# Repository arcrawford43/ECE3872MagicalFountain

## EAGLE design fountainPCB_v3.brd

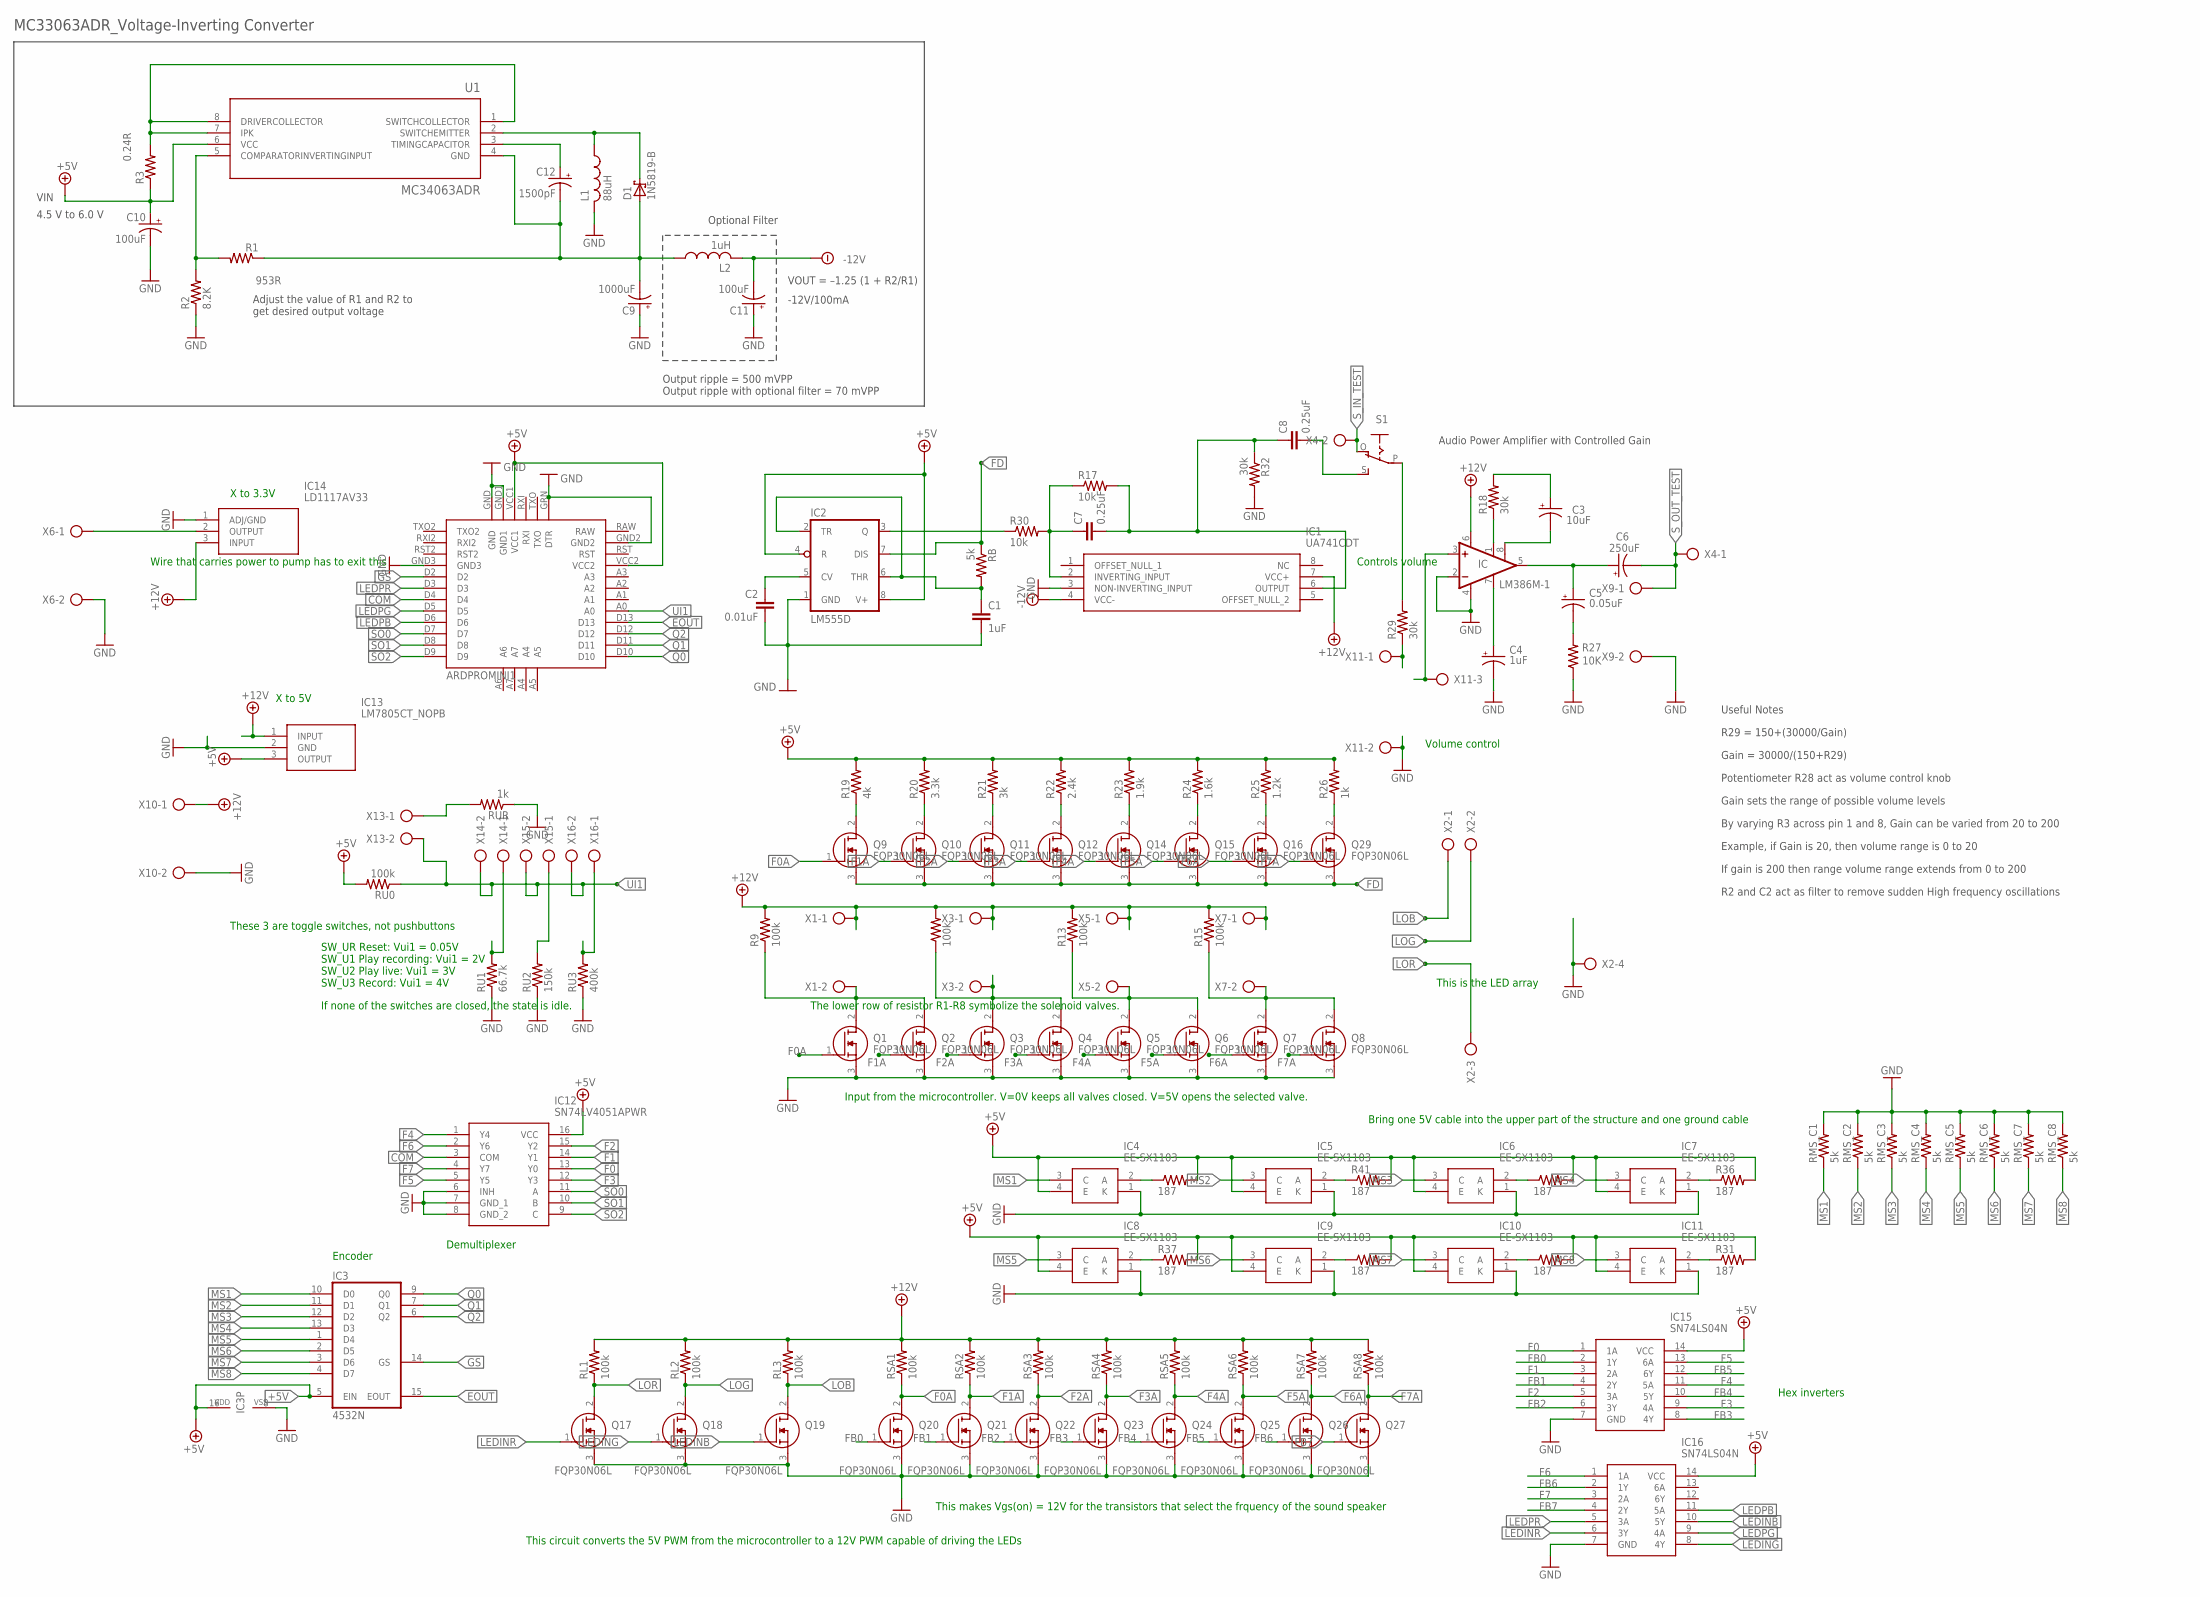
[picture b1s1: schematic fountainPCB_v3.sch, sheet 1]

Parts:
ARDPROMINI1: ARDUINOPROMINI
C1: 1uF; C0805
C2: 0.01uF; C0805
C3: 10uF; 085CS_1AR
C4: 1uF; 085CS_1AR
C5: 0.05uF; 085CS_1AR
C6: 250uF; 085CS_1AR
C7, C8: 0.25uF; C0805
C9: 1000uF; E7,5-16
C10, C11: 100uF; E2,5-6E
C12: 1500pF; E2,5-6E
D1: 1N5819-B; DO41-7.6
IC: LM386M-1; SO08
IC1: UA741CDT; SOIC127P600X175-8N
IC2: LM555D; SO08
IC3: 4532N; DIL16
IC4, IC5, IC6, IC7, IC8, IC9, IC10, IC11: EE-SX1103; EESX1103
IC12: SN74LV4051APWR; SOP65P640X120-16N
IC13: LM7805CT_NOPB; TO254P470X1028X1955-3P
IC14: LD1117AV33; TO255P460X1020X2008-3P
IC15, IC16: SN74LS04N; DIP794W53P254L1930H508Q14N
L1: 88uH; L3216C
L2: 1uH; L3216C
Q1, Q2, Q3, Q4, Q5, Q6, Q7, Q8, Q9, Q10, Q11, Q12, Q14, Q15, Q16, Q17, Q18, Q19, Q20, Q21, Q22, Q23, Q24, Q25, Q26, Q27, Q29: FQP30N06L; TO254P470X1016X2019-3P
R1: 953R; M0805
R2: 8.2K; M0805
R3: 0.24R; M0805
R9, R11, R13, R15: 100k; R0805
R17, R30: 10k; R0805
R18, R29, R32: 30k; R0805
R19: 4k; R0805
R20: 3.3k; R0805
R21: 3k; R0805
R22: 2.4k; R0805
R23: 1.9k; R0805
R24: 1.6k; R0805
R25: 1.2k; R0805
R26: 1k; R0805
R27: 10K; M0805
R31, R34, R36, R37, R40, R41, R42, R44: 187; R0805
RB: 5k; R0805
RL1, RL2, RL3: 100k; R0805
RMS_C1, RMS_C2, RMS_C3, RMS_C4, RMS_C5, RMS_C6, RMS_C7, RMS_C8: 5k; R0805
RSA1, RSA2, RSA3, RSA4, RSA5, RSA6, RSA7, RSA8: 100k; R0805
RU0: 100k; R0805
RU1: 66.7k; R0805
RU2: 150k; R0805
RU3: 400k; R0805
RUR: 1k; R0805
S1: EG1218S; EG1218
U1: MC34063ADR; D8
X1, X3, X4, X5, X6, X7, X9, X10, X13, X14, X15, X16: AK300/2
X2: AK300/4
X11: AK300/3

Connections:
+5V: ARDPROMINI1.VCC1, ARDPROMINI1.VCC2, C10.+, IC2.4 (R), IC2.8 (V+), IC3.5 (EIN), IC3.16 (VDD), IC4.4 (E), IC5.4 (E), IC6.4 (E), IC7.4 (E), IC8.4 (E), IC9.4 (E), IC10.4 (E), IC11.4 (E), IC12.16 (VCC), IC13.3 (OUTPUT), IC15.14 (VCC), IC16.14 (VCC), R3.1, R19.2, R20.2, R21.2, R22.2, R23.2, R24.2, R25.2, R26.2, R31.2, R34.2, R36.2, R37.2, R40.2, R41.2, R42.2, R44.2, RU0.2, U1.6 (VCC)
+12V: IC.6 (VS), IC1.7 (VCC+), IC13.1 (INPUT), IC14.3 (INPUT), R9.2, R11.2, R13.2, R15.2, RL1.2, RL2.2, RL3.2, RSA1.2, RSA2.2, RSA3.2, RSA4.2, RSA5.2, RSA6.2, RSA7.2, RSA8.2, X1.1, X3.1, X5.1, X7.1, X10.1
+12V1: IC14.2 (OUTPUT), X6.1
-12V: C11.-, IC1.4 (VCC-), L2.2
COM: ARDPROMINI1.D4, IC12.3 (COM)
EOUT: ARDPROMINI1.D13, IC3.15 (EOUT)
F0: IC12.13 (Y0), IC15.1 (1A)
F0A: Q1.1 (G), Q9.1 (G), Q20.2 (D), RSA1.1
F1: IC12.14 (Y1), IC15.3 (2A)
F1A: Q2.1 (G), Q10.1 (G), Q21.2 (D), RSA2.1
F2: IC12.15 (Y2), IC15.5 (3A)
F2A: Q3.1 (G), Q11.1 (G), Q22.2 (D), RSA3.1
F3: IC12.12 (Y3), IC15.9 (4A)
F3A: Q4.1 (G), Q12.1 (G), Q23.2 (D), RSA4.1
F4: IC12.1 (Y4), IC15.11 (5A)
F4A: Q5.1 (G), Q14.1 (G), Q24.2 (D), RSA5.1
F5: IC12.5 (Y5), IC15.13 (6A)
F5A: Q6.1 (G), Q15.1 (G), Q25.2 (D), RSA6.1
F6: IC12.2 (Y6), IC16.1 (1A)
F6A: Q7.1 (G), Q16.1 (G), Q26.2 (D), RSA7.1
F7: IC12.4 (Y7), IC16.3 (2A)
F7A: Q8.1 (G), Q27.2 (D), Q29.1 (G), RSA8.1
FB0: IC15.2 (1Y), Q20.1 (G)
FB1: IC15.4 (2Y), Q21.1 (G)
FB2: IC15.6 (3Y), Q22.1 (G)
FB3: IC15.8 (4Y), Q23.1 (G)
FB4: IC15.10 (5Y), Q24.1 (G)
FB5: IC15.12 (6Y), Q25.1 (G)
FB6: IC16.2 (1Y), Q26.1 (G)
FB7: IC16.4 (2Y), Q27.1 (G)
FD: IC2.7 (DIS), Q9.3 (S), Q10.3 (S), Q11.3 (S), Q12.3 (S), Q14.3 (S), Q15.3 (S), Q16.3 (S), Q29.3 (S), RB.1
GND: ARDPROMINI1.GND, ARDPROMINI1.GND1, ARDPROMINI1.GND2, ARDPROMINI1.GND3, ARDPROMINI1.GRN (DTR), C1.2, C2.2, C4.-, C9.+, C10.-, C11.+, IC.2 (-IN), IC.4 (GND), IC1.3 (NON-INVERTING_INPUT), IC2.1 (GND), IC3.8 (VSS), IC4.1 (K), IC5.1 (K), IC6.1 (K), IC7.1 (K), IC8.1 (K), IC9.1 (K), IC10.1 (K), IC11.1 (K), IC12.6 (INH), IC12.7 (GND_1), IC12.8 (GND_2), IC13.2 (GND), IC14.1 (ADJ/GND), IC15.7 (GND), IC16.7 (GND), L1.2, Q1.3 (S), Q2.3 (S), Q3.3 (S), Q4.3 (S), Q5.3 (S), Q6.3 (S), Q7.3 (S), Q8.3 (S), Q17.3 (S), Q18.3 (S), Q19.3 (S), Q20.3 (S), Q21.3 (S), Q22.3 (S), Q23.3 (S), Q24.3 (S), Q25.3 (S), Q26.3 (S), Q27.3 (S), R2.1, R27.1, R32.2, RMS_C1.2, RMS_C2.2, RMS_C3.2, RMS_C4.2, RMS_C5.2, RMS_C6.2, RMS_C7.2, RMS_C8.2, RU1.1, RU2.1, RU3.1, RUR.1, X2.4, X6.2, X9.2, X10.2, X11.2
GS: ARDPROMINI1.D2, IC3.14 (GS)
LEDINB: IC16.10 (5Y), Q19.1 (G)
LEDING: IC16.8 (4Y), Q18.1 (G)
LEDINR: IC16.6 (3Y), Q17.1 (G)
LEDPB: ARDPROMINI1.D6, IC16.11 (5A)
LEDPG: ARDPROMINI1.D5, IC16.9 (4A)
LEDPR: ARDPROMINI1.D3, IC16.5 (3A)
LOB: Q19.2 (D), RL3.1, X2.1
LOG: Q18.2 (D), RL2.1, X2.2
LOR: Q17.2 (D), RL1.1, X2.3
MS1: IC3.10 (D0), IC4.3 (C), RMS_C1.1
MS2: IC3.11 (D1), IC5.3 (C), RMS_C2.1
MS3: IC3.12 (D2), IC6.3 (C), RMS_C3.1
MS4: IC3.13 (D3), IC7.3 (C), RMS_C4.1
MS5: IC3.1 (D4), IC8.3 (C), RMS_C5.1
MS6: IC3.2 (D5), IC9.3 (C), RMS_C6.1
MS7: IC3.3 (D6), IC10.3 (C), RMS_C7.1
MS8: IC3.4 (D7), IC11.3 (C), RMS_C8.1
unnamed: Q1.2 (D), Q2.2 (D), R9.1, X1.2
unnamed: Q3.2 (D), Q4.2 (D), R11.1, X3.2
unnamed: R3.2, U1.1 (SWITCHCOLLECTOR), U1.7 (IPK), U1.8 (DRIVERCOLLECTOR)
unnamed: Q5.2 (D), Q6.2 (D), R13.1, X5.2
unnamed: D1.C, L1.1, U1.2 (SWITCHEMITTER)
unnamed: Q7.2 (D), Q8.2 (D), R15.1, X7.2
unnamed: C12.+, U1.3 (TIMINGCAPACITOR)
unnamed: C2.1, IC2.5 (CV)
unnamed: IC4.2 (A), R44.1
unnamed: C1.1, IC2.2 (TR), IC2.6 (THR), RB.2
unnamed: Q9.2 (D), R19.1
unnamed: Q10.2 (D), R20.1
unnamed: Q11.2 (D), R21.1
unnamed: Q12.2 (D), R22.1
unnamed: Q14.2 (D), R23.1
unnamed: Q15.2 (D), R24.1
unnamed: Q16.2 (D), R25.1
unnamed: Q29.2 (D), R26.1
unnamed: C4.+, IC.7 (BYPASS)
unnamed: C5.+, C6.+, IC.5 (OUT)
unnamed: C3.-, IC.8 (GAIN)
unnamed: IC.3 (+IN), X11.3
unnamed: C5.-, R27.2
unnamed: IC.1 (GAIN), R18.1
unnamed: C3.+, R18.2
unnamed: R29.2, S1.P
unnamed: C7.1, IC1.2 (INVERTING_INPUT), R17.1, R30.2
unnamed: C7.2, C8.1, IC1.6 (OUTPUT), R17.2, R32.1
unnamed: RUR.2, X13.1
unnamed: IC8.2 (A), R37.1
unnamed: IC5.2 (A), R41.1
unnamed: RU3.2, X16.1
unnamed: RU2.2, X15.1
unnamed: RU1.2, X14.1
unnamed: IC6.2 (A), R42.1
unnamed: IC7.2 (A), R36.1
unnamed: R1.2, R2.2, U1.5 (COMPARATORINVERTINGINPUT)
unnamed: IC11.2 (A), R31.1
unnamed: IC10.2 (A), R40.1
unnamed: IC9.2 (A), R34.1
unnamed: C9.-, C12.-, D1.A, L2.1, R1.1, U1.4 (GND)
unnamed: R29.1, X11.1
unnamed: C8.2, S1.S
unnamed: IC2.3 (Q), R30.1
Q0: ARDPROMINI1.D10, IC3.9 (Q0)
Q1: ARDPROMINI1.D11, IC3.7 (Q1)
Q2: ARDPROMINI1.D12, IC3.6 (Q2)
SO0: ARDPROMINI1.D7, IC12.11 (A)
SO1: ARDPROMINI1.D8, IC12.10 (B)
SO2: ARDPROMINI1.D9, IC12.9 (C)
S_IN_TEST: S1.O, X4.2
S_OUT_TEST: C6.-, X4.1, X9.1
UI1: ARDPROMINI1.A0, RU0.1, X13.2, X14.2, X15.2, X16.2

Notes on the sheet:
The lower row of resistor R1-R8 symbolize the solenoid valves.
Input from the microcontroller. V=0V keeps all valves closed. V=5V opens the selected valve.
Audio Power Amplifier with Controlled Gain
Potentiometer R28 act as volume control knob
R2 and C2 act as filter to remove sudden High frequency oscillations
Gain sets the range of possible volume levels
Gain = 30000/(150+R29)
R29 = 150+(30000/Gain)
Useful Notes
By varying R3 across pin 1 and 8, Gain can be varied from 20 to 200
Example, if Gain is 20, then volume range is 0 to 20
If gain is 200 then range volume range extends from 0 to 200
Controls volume
These 3 are toggle switches, not pushbuttons
SW_UR Reset: Vui1 = 0.05V SW_U1 Play recording: Vui1 = 2V SW_U2 Play live: Vui1 = 3V SW_U3 Record: Vui1 = 4V
If none of the switches are closed, the state is idle.
This is the LED array
This makes Vgs(on) = 12V for the transistors that select the frquency of the sound speaker
This circuit converts the 5V PWM from the microcontroller to a 12V PWM capable of driving the LEDs
Volume control
Hex inverters
Demultiplexer
Encoder
Bring one 5V cable into the upper part of the structure and one ground cable
X to 3.3V
X to 5V
Wire that carries power to pump has to exit this
4.5 V to 6.0 V
-12V/100mA
Optional Filter
VOUT = –1.25 (1 + R2/R1)
MC33063ADR_Voltage-Inverting Converter
VIN
Adjust the value of R1 and R2 to get desired output voltage
Output ripple = 500 mVPP Output ripple with optional filter = 70 mVPP

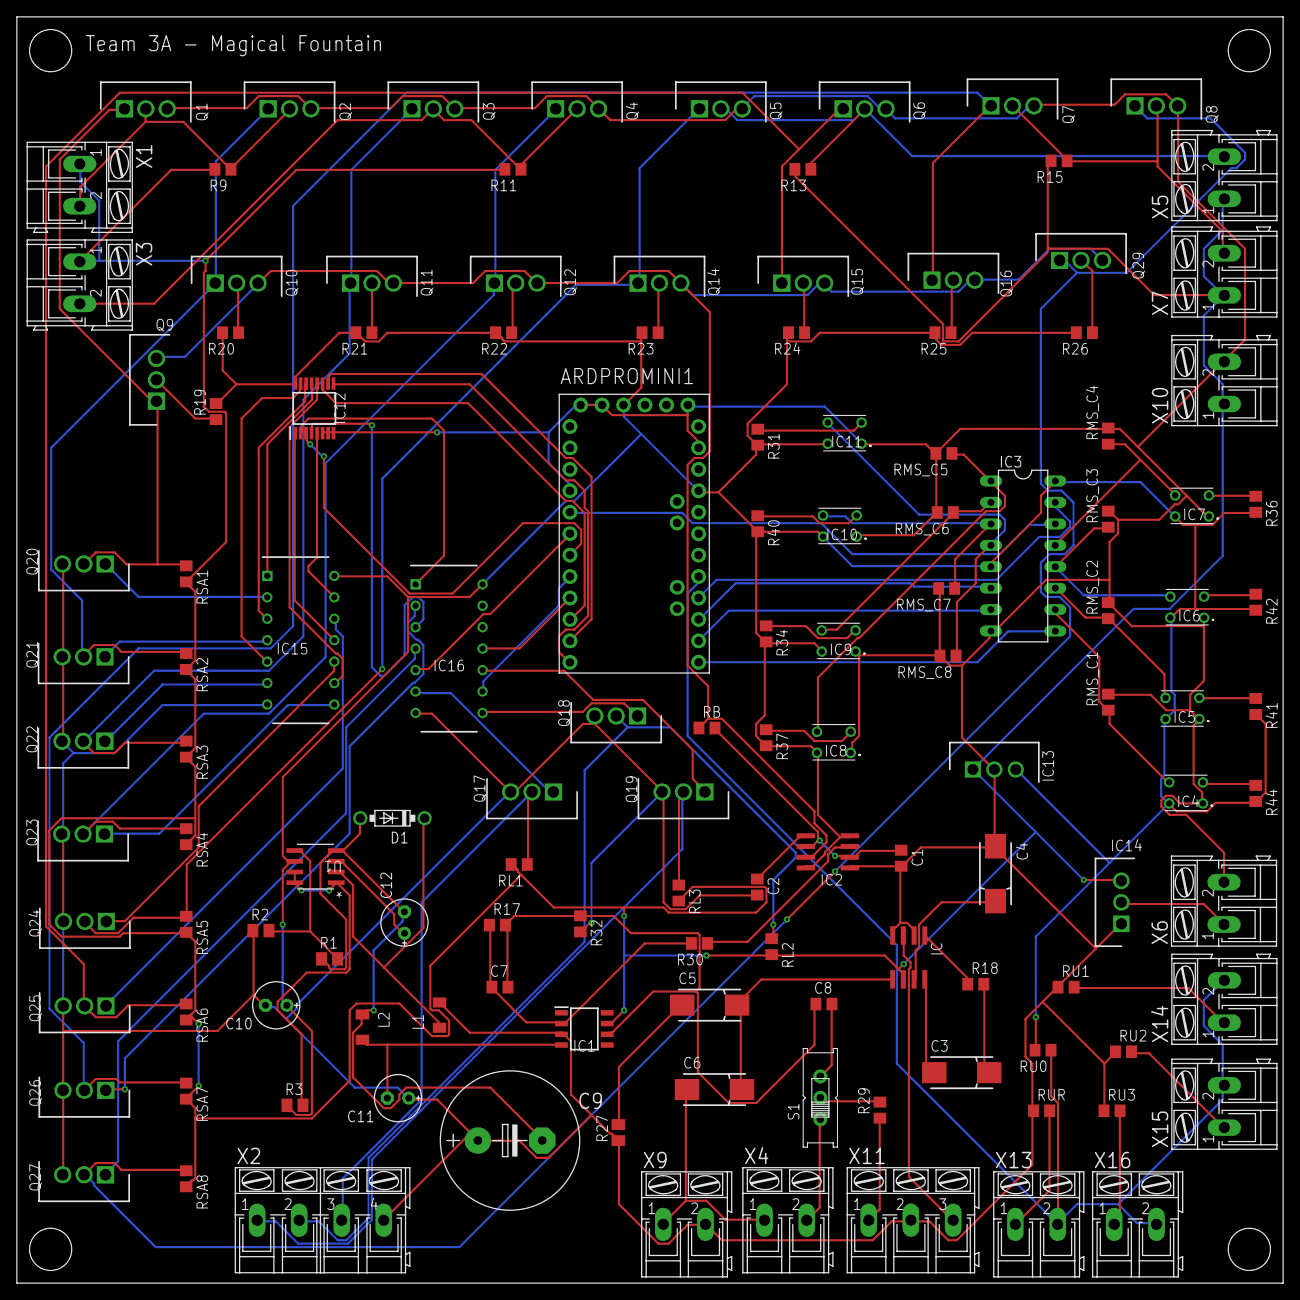
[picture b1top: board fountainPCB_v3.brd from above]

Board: 2 copper layers, 150.0 x 150.0 mm, 130 parts (0 on the bottom side), 103 nets.

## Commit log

2020-10-15 Fountain schematic for purposes of testing
    Does not include the board file, reorganized for ease of comprehension.
2020-10-15 Resistor values updated
2020-10-16 Updated resistors
    Updated all resistors, may be tested.
2020-10-20 Tuning of resistors and aesthetic edits
2020-10-20 Add files via upload
    Tuning of resistors and aesthetic edits
2020-10-20 schematic reflecting PCB
2020-10-29 updated resistors
2020-10-29 Valves subcircuit changed
    Using AND gates to control signal adds 1 extra digital output from the microcontroller. The new circuit is in the top of the schametic.
